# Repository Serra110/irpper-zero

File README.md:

# Irper-Zero

Irper-Zero is a small handheld device ran on the Raspberry Pi Pico that can capture infrared (IR) signals and save them to a microSD card for later use. The project combines infrared tools with a small OLED display and games, being focused on the display, as everything involves it. It currently includes two games, with the possibility of adding more in the future by loading compatible game files from the microSD card.

## Features

- **IR Signal Capture:** Receive infrared signals using an IR receiver.
- **microSD Storage:** Save captured IR signals to a microSD card.
- **OLED Display:** Display menus, 2d viewer of signals and games.
- **Built-in Games:** Includes two games for entertainment, both 1v1.
- **Expandable Game Library:** Designed to support additional games loaded from the microSD card, provided they use a compatible format, WIP.
- **IR Transmission:** Is able to send the signals that are saved in the microSD.

## Hardware Design

The device is built around the Raspberry Pi Pico, which handles the display, buttons, infrared signal capture and microSD storage.

### 3D Model

A 3D representation of the project designed in KiCad.

### Schematic

## Controls

SW1- Select/Confirm
SW2- Back

SW3- Player 1 up/Menu up
SW4- Player 1 down/Menu down

SW5- Player 2 up
SW6- Player 2 down

## Infrared Tools

The IR tool allows the device to capture infrared signals from compatible signals (not encrypted basically) and save the recorded data to a microSD card.
After, the device will be able to read the microSD and send those signals as well.

## Games

Irper-Zero includes two built-in games that can be played directly on the device using its display and controls, pong and spam game (the one to reach the top first wins)
## Code

The firmware runs on the Raspberry Pi Pico and manages the display, controls, infrared signal capture, microSD card and games.
It is also supposed to reads the signals and show on the display the frequency, basically an IR signal viewer

## AI usage
AI was used to generate some code including the UI since I do not know how to do it myself, I defined everything and woke every pin up myself.

## About the Project
The project is the first one to be focused entirely on frequencies, not counting the game, IR signals and the display. This was the first "alone" project to be made since I didn't follow a tutorial, and just took consideration.

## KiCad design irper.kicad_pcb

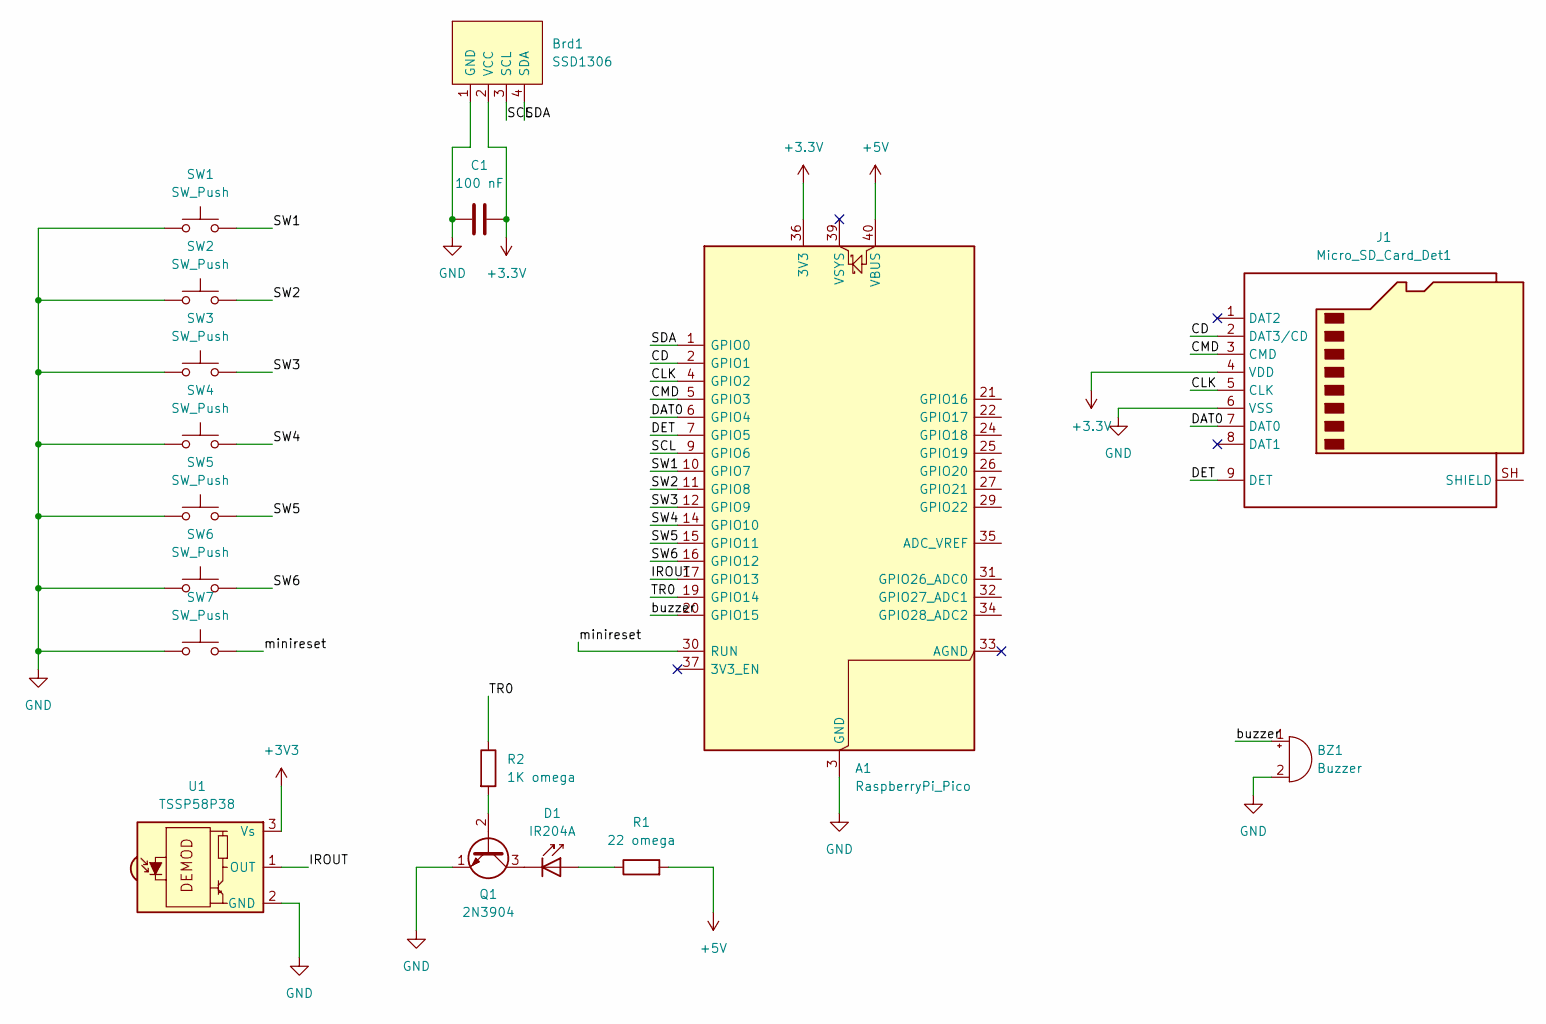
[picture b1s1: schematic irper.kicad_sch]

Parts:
A1: RaspberryPi_Pico; RaspberryPi_Pico_Common
BZ1: Buzzer
Brd1: SSD1306; 128x64OLED
C1: 100 nF; CP_Elec_3x5.3
D1: IR204A; LED_D3.0mm_IRBlack
J1: Micro_SD_Card_Det1; microSD_HC_Hirose_DM3AT-SF-PEJM5
Q1: 2N3904; TO-92_Inline
R1: 22 omega; R_Axial_DIN0204_L3.6mm_D1.6mm_P7.62mm_Horizontal
R2: 1K omega; R_Axial_DIN0204_L3.6mm_D1.6mm_P7.62mm_Horizontal
SW1, SW2, SW3, SW4, SW5, SW6, SW7: SW_Push; SW_PUSH_6mm_H5mm
U1: TSSP58P38; Vishay_MINICAST-3Pin

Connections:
+3.3V: A1.36 (3V3), Brd1.2 (VCC), C1.2, J1.4 (VDD)
+3V3: U1.3 (Vs)
+5V: A1.40 (VBUS), R1.2
/CD: A1.2 (GPIO1), J1.2 (DAT3/CD)
/CLK: A1.4 (GPIO2), J1.5 (CLK)
/CMD: A1.5 (GPIO3), J1.3 (CMD)
/DAT0: A1.6 (GPIO4), J1.7 (DAT0)
/DET: A1.7 (GPIO5), J1.9 (DET)
/IROUT: A1.17 (GPIO13), U1.1 (OUT)
/SCL: A1.9 (GPIO6), Brd1.3 (SCL)
/SDA: A1.1 (GPIO0), Brd1.4 (SDA)
/SW1: A1.10 (GPIO7), SW1.2
/SW2: A1.11 (GPIO8), SW2.2
/SW3: A1.12 (GPIO9), SW3.2
/SW4: A1.14 (GPIO10), SW4.2
/SW5: A1.15 (GPIO11), SW5.2
/SW6: A1.16 (GPIO12), SW6.2
/TR0: A1.19 (GPIO14), R2.1
/buzzer: A1.20 (GPIO15), BZ1.1 (+)
/minireset: A1.30 (RUN), SW7.2
GND: A1.3 (GND), A1.8 (GND), A1.13 (GND), A1.18 (GND), A1.23 (GND), A1.28 (GND), A1.38 (GND), BZ1.2 (-), Brd1.1 (GND), C1.1, J1.6 (VSS), Q1.1 (E), SW1.1, SW2.1, SW3.1, SW4.1, SW5.1, SW6.1, SW7.1, U1.2 (GND)
unnamed: D1.2 (A), R1.1
unnamed: D1.1 (K), Q1.3 (C)
unnamed: Q1.2 (B), R2.2

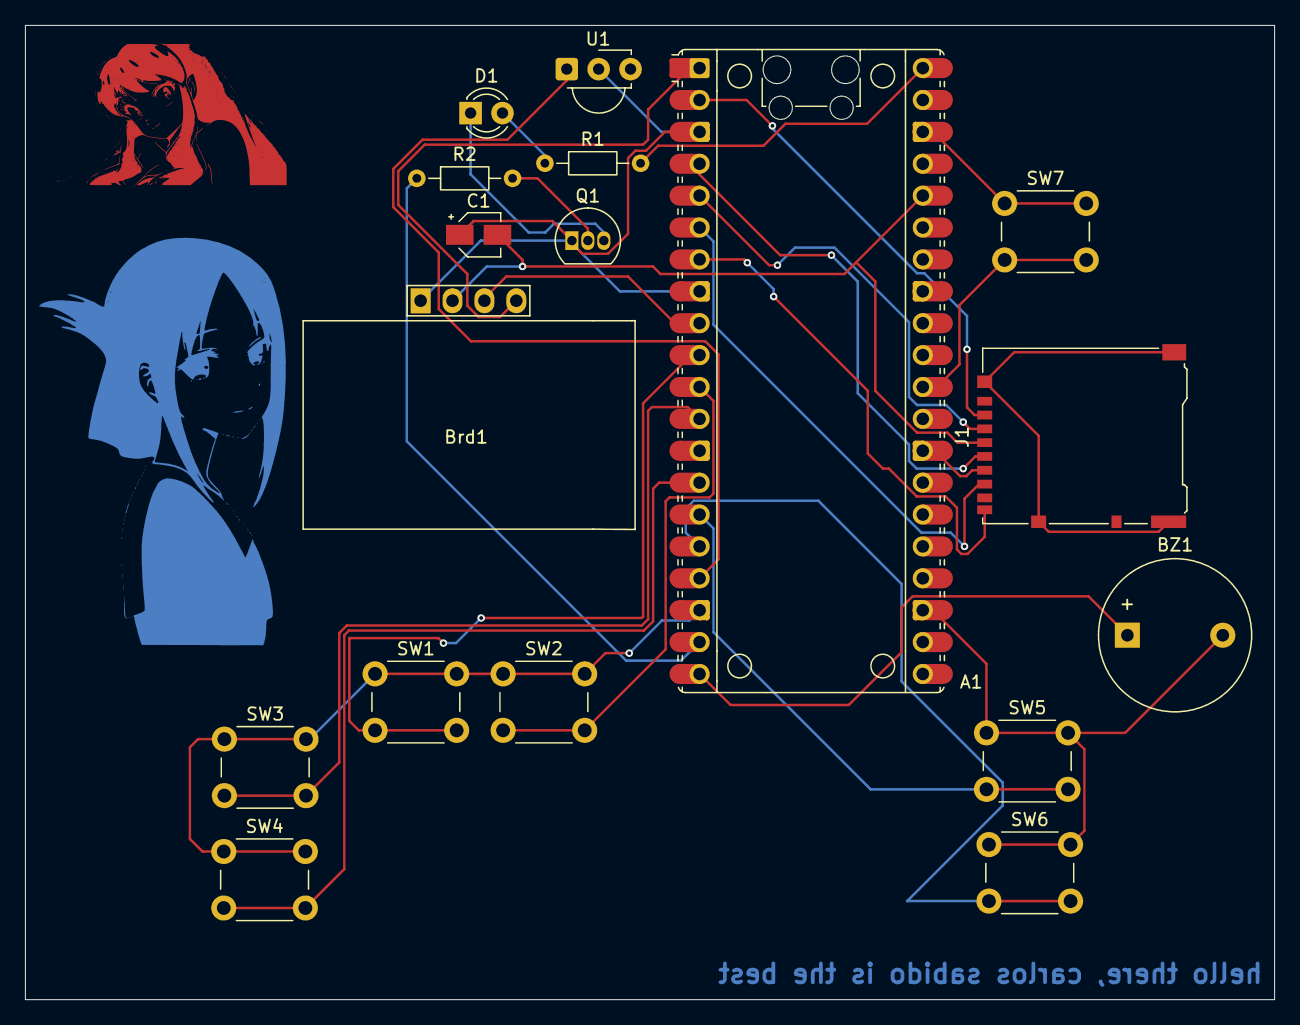
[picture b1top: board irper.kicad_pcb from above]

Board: 2 copper layers, 99.5 x 77.6 mm, 17 parts (0 on the bottom side), 23 nets.

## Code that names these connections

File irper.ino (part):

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// sd card:
#define PIN_SD_CS 1 //CD
#define PIN_SD_SCK 2 //CLK
#define PIN_SD_MOSI 3 //CMD
#define PIN_SD_MISO 4 //DAT0, miso is a soup for me
#define PIN_SD_DET 5 
// switches:
#define PIN_SW1 6  // Menu/Select
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#define PIN_SW5 10 // Player 2 Up
#define PIN_SW6 11 // Player 2 Down
//misc
#define buzzer 15
// swtich 7 is the reset button, it is not connected to the microcontroller, but to the reset pin of the microcontroller, so it will reset the microcontroller when pressed
// IR stuff:
#define PIN_IR_RX 13 // thing that reads IR signals
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    for (int i = 0; i < 6; i++) {
        pinMode(buttonPins[i], INPUT_PULLUP);
    }
    pinMode(PIN_SD_DET, INPUT_PULLUP); // SD CARD DET INPUT
    // ir stuff
    pinMode(PIN_IR_TX, OUTPUT);
    digitalWrite(PIN_IR_TX, LOW);
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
